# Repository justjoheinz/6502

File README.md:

# 6502 Microcomputer

## Bill of materials

[BOM](6502.csv)

## Schematic

## PCB

### Mainboard

### Prototype Board

### Status

| Version | Status | Comment |
|---------|--------|---------|
| v1.0.0  | unverified | boards send for production |

## Memory maps

| Type | From | To       | Comments |
|------|------|----------|----------|
| RAM  | 0x0000 | 0x3FFF |          |
| VIA  | 0x6000 |        | A14, A15 - Registers via A0 - A3 |
| ROM  | 0x8000 | 0xFFFF | A15 High |

## ROM Source Code

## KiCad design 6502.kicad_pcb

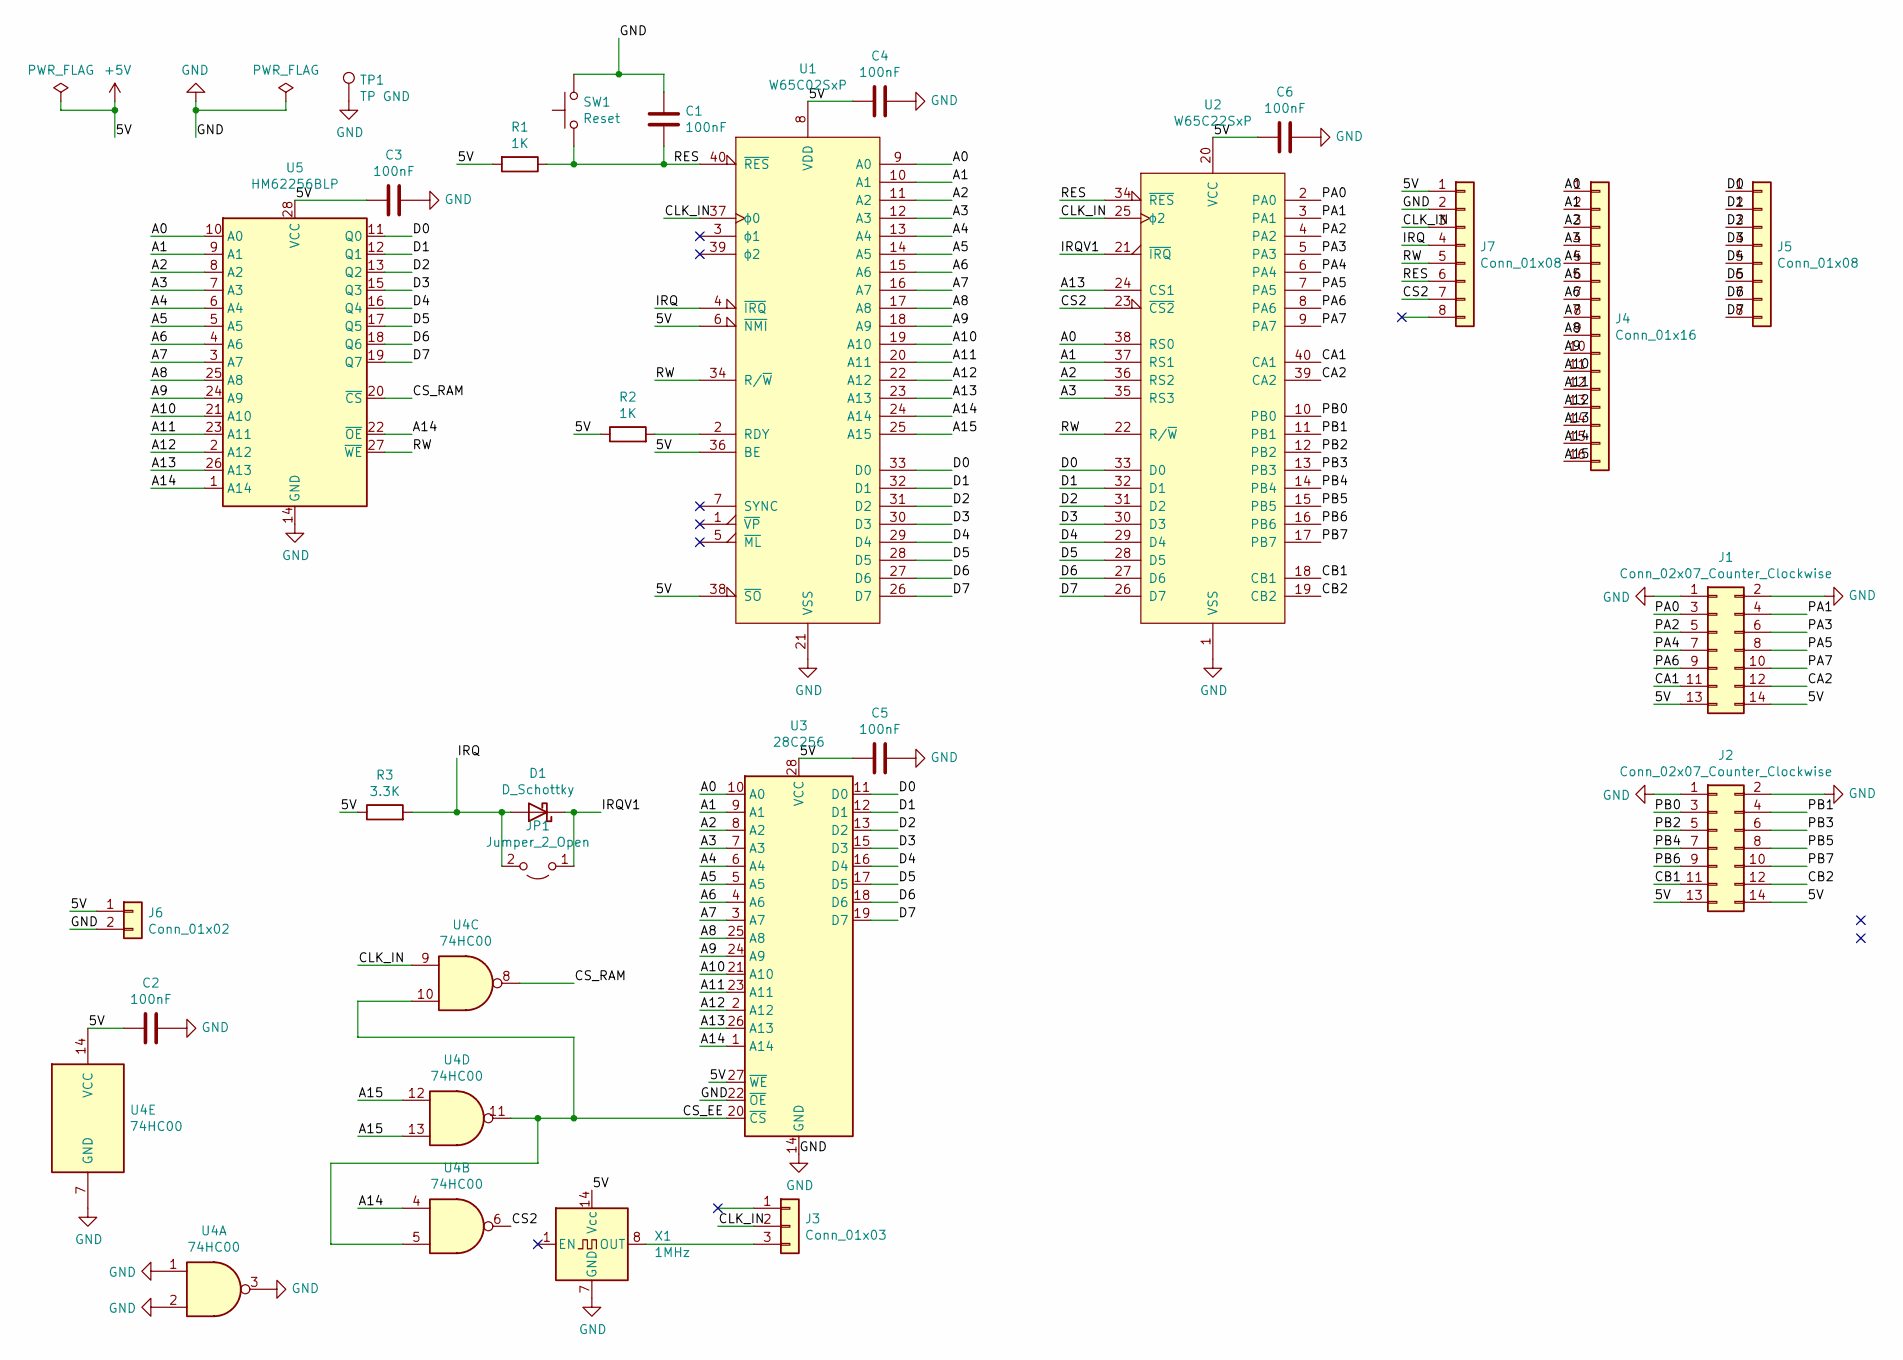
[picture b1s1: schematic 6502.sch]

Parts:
C1, C2, C3, C4, C5, C6: 100nF; C_Disc_D4.3mm_W1.9mm_P5.00mm
D1: D_Schottky; D_DO-35_SOD27_P7.62mm_Horizontal
J1, J2: Conn_02x07_Counter_Clockwise; PinHeader_2x07_P2.54mm_Horizontal
J3: Conn_01x03; PinHeader_1x03_P2.54mm_Vertical
J4: Conn_01x16; PinHeader_1x16_P2.54mm_Vertical
J5, J7: Conn_01x08; PinHeader_1x08_P2.54mm_Vertical
J6: Conn_01x02; PinHeader_1x02_P2.54mm_Vertical
JP1: Jumper_2_Open; TestPoint_2Pads_Pitch2.54mm_Drill0.8mm
R1, R2: 1K; R_Axial_DIN0204_L3.6mm_D1.6mm_P7.62mm_Horizontal
R3: 3.3K; R_Axial_DIN0204_L3.6mm_D1.6mm_P7.62mm_Horizontal
SW1: Reset; SW_PUSH_6mm
TP1: TP GND; TestPoint_Pad_2.0x2.0mm
U1: W65C02SxP; DIP-40_W15.24mm_Socket_LongPads
U2: W65C22SxP; DIP-40_W15.24mm_Socket_LongPads
U3: 28C256; DIP_Socket-28_W11.9_W12.7_W15.24_W17.78_W18.5_3M_228-1277-0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
U4: 74HC00; DIP-14_W7.62mm_Socket_LongPads
U5: HM62256BLP; DIP-28_W15.24mm_Socket_LongPads
X1: 1MHz; Oscillator_DIP-14

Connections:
+5V: C2.2, C3.2, C4.2, C5.1, C6.1, J1.13, J1.14, J2.13, J2.14, J6.1, J7.1, R1.2, R2.1, R3.1, U1.6 (~NMI), U1.8 (VDD), U1.36 (BE), U1.38 (~SO), U2.20 (VCC), U3.27 (~WE), U3.28 (VCC), U4.14 (VCC), U5.28 (VCC), X1.14 (Vcc)
/A0: J4.1, U1.9 (A0), U2.38 (RS0), U3.10 (A0), U5.10 (A0)
/A1: J4.2, U1.10 (A1), U2.37 (RS1), U3.9 (A1), U5.9 (A1)
/A2: J4.3, U1.11 (A2), U2.36 (RS2), U3.8 (A2), U5.8 (A2)
/A3: J4.4, U1.12 (A3), U2.35 (RS3), U3.7 (A3), U5.7 (A3)
/A4: J4.5, U1.13 (A4), U3.6 (A4), U5.6 (A4)
/A5: J4.6, U1.14 (A5), U3.5 (A5), U5.5 (A5)
/A6: J4.7, U1.15 (A6), U3.4 (A6), U5.4 (A6)
/A7: J4.8, U1.16 (A7), U3.3 (A7), U5.3 (A7)
/A8: J4.9, U1.17 (A8), U3.25 (A8), U5.25 (A8)
/A9: J4.10, U1.18 (A9), U3.24 (A9), U5.24 (A9)
/A10: J4.11, U1.19 (A10), U3.21 (A10), U5.21 (A10)
/A11: J4.12, U1.20 (A11), U3.23 (A11), U5.23 (A11)
/A12: J4.13, U1.22 (A12), U3.2 (A12), U5.2 (A12)
/A13: J4.14, U1.23 (A13), U2.24 (CS1), U3.26 (A13), U5.26 (A13)
/A14: J4.15, U1.24 (A14), U3.1 (A14), U4.4, U5.1 (A14), U5.22 (~OE)
/A15: J4.16, U1.25 (A15), U4.12, U4.13
/CA1: J1.11, U2.40 (CA1)
/CA2: J1.12, U2.39 (CA2)
/CB1: J2.11, U2.18 (CB1)
/CB2: J2.12, U2.19 (CB2)
/CLK_IN: J3.2, J7.3, U1.37 (ϕ0), U2.25 (ϕ2), U4.9
/CS2: J7.7, U2.23 (~CS2), U4.6
/CS_EE: U3.20 (~CS), U4.5, U4.10, U4.11
/CS_RAM: U4.8, U5.20 (~CS)
/D0: J5.1, U1.33 (D0), U2.33 (D0), U3.11 (D0), U5.11 (Q0)
/D1: J5.2, U1.32 (D1), U2.32 (D1), U3.12 (D1), U5.12 (Q1)
/D2: J5.3, U1.31 (D2), U2.31 (D2), U3.13 (D2), U5.13 (Q2)
/D3: J5.4, U1.30 (D3), U2.30 (D3), U3.15 (D3), U5.15 (Q3)
/D4: J5.5, U1.29 (D4), U2.29 (D4), U3.16 (D4), U5.16 (Q4)
/D5: J5.6, U1.28 (D5), U2.28 (D5), U3.17 (D5), U5.17 (Q5)
/D6: J5.7, U1.27 (D6), U2.27 (D6), U3.18 (D6), U5.18 (Q6)
/D7: J5.8, U1.26 (D7), U2.26 (D7), U3.19 (D7), U5.19 (Q7)
/IRQ: D1.2 (A), J7.4, JP1.2 (B), R3.2, U1.4 (~IRQ)
/IRQV1: D1.1 (K), JP1.1 (A), U2.21 (~IRQ)
/PA0: J1.3, U2.2 (PA0)
/PA1: J1.4, U2.3 (PA1)
/PA2: J1.5, U2.4 (PA2)
/PA3: J1.6, U2.5 (PA3)
/PA4: J1.7, U2.6 (PA4)
/PA5: J1.8, U2.7 (PA5)
/PA6: J1.9, U2.8 (PA6)
/PA7: J1.10, U2.9 (PA7)
/PB0: J2.3, U2.10 (PB0)
/PB1: J2.4, U2.11 (PB1)
/PB2: J2.5, U2.12 (PB2)
/PB3: J2.6, U2.13 (PB3)
/PB4: J2.7, U2.14 (PB4)
/PB5: J2.8, U2.15 (PB5)
/PB6: J2.9, U2.16 (PB6)
/PB7: J2.10, U2.17 (PB7)
/RES: C1.2, J7.6, R1.1, SW1.1, U1.40 (~RES), U2.34 (~RES)
/RW: J7.5, U1.34 (R/~W), U2.22 (R/~W), U5.27 (~WE)
GND: C1.1, C2.1, C3.1, C4.1, C5.2, C6.2, J1.1, J1.2, J2.1, J2.2, J6.2, J7.2, SW1.2, TP1.1, U1.21 (VSS), U2.1 (VSS), U3.14 (GND), U3.22 (~OE), U4.1, U4.2, U4.3, U4.7 (GND), U5.14 (GND), X1.7 (GND)
unnamed: J3.3, X1.8 (OUT)
unnamed: R2.2, U1.2 (RDY)

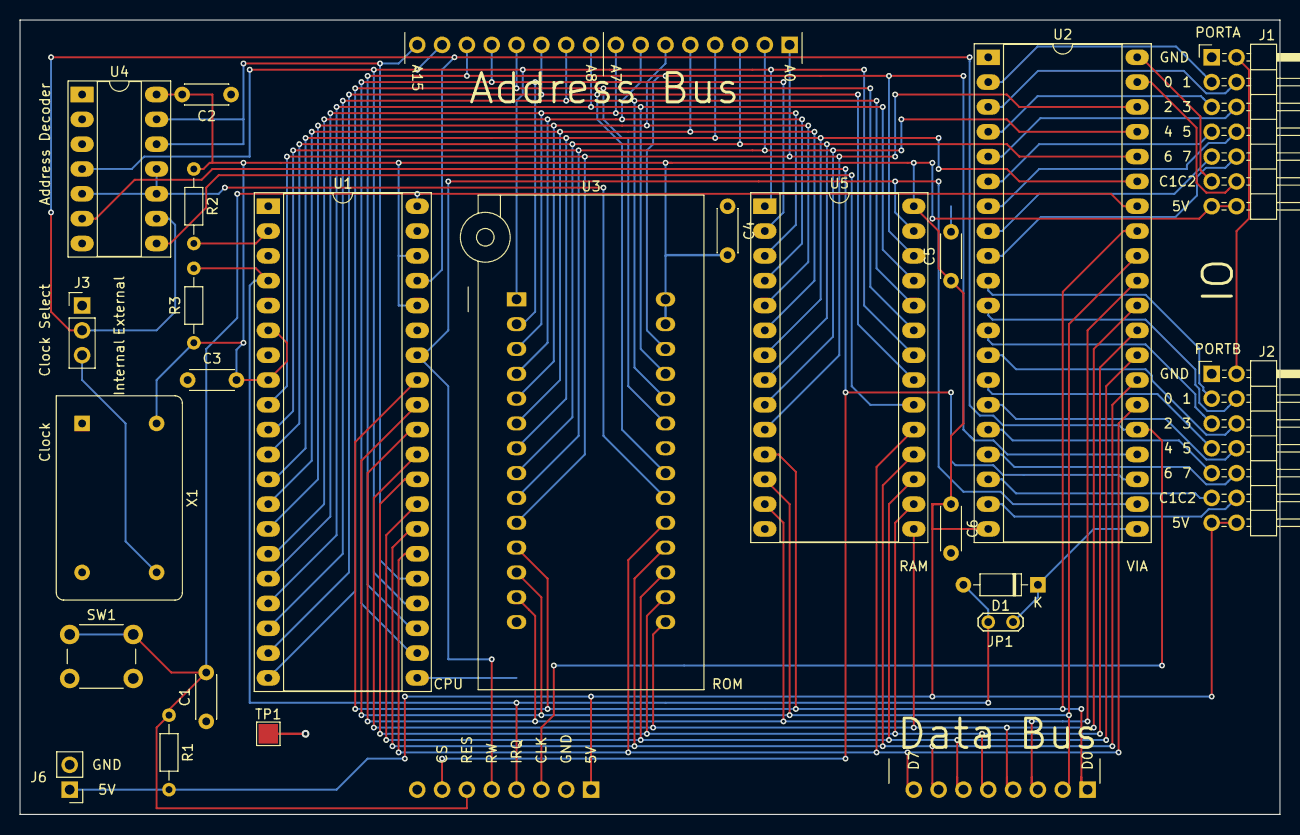
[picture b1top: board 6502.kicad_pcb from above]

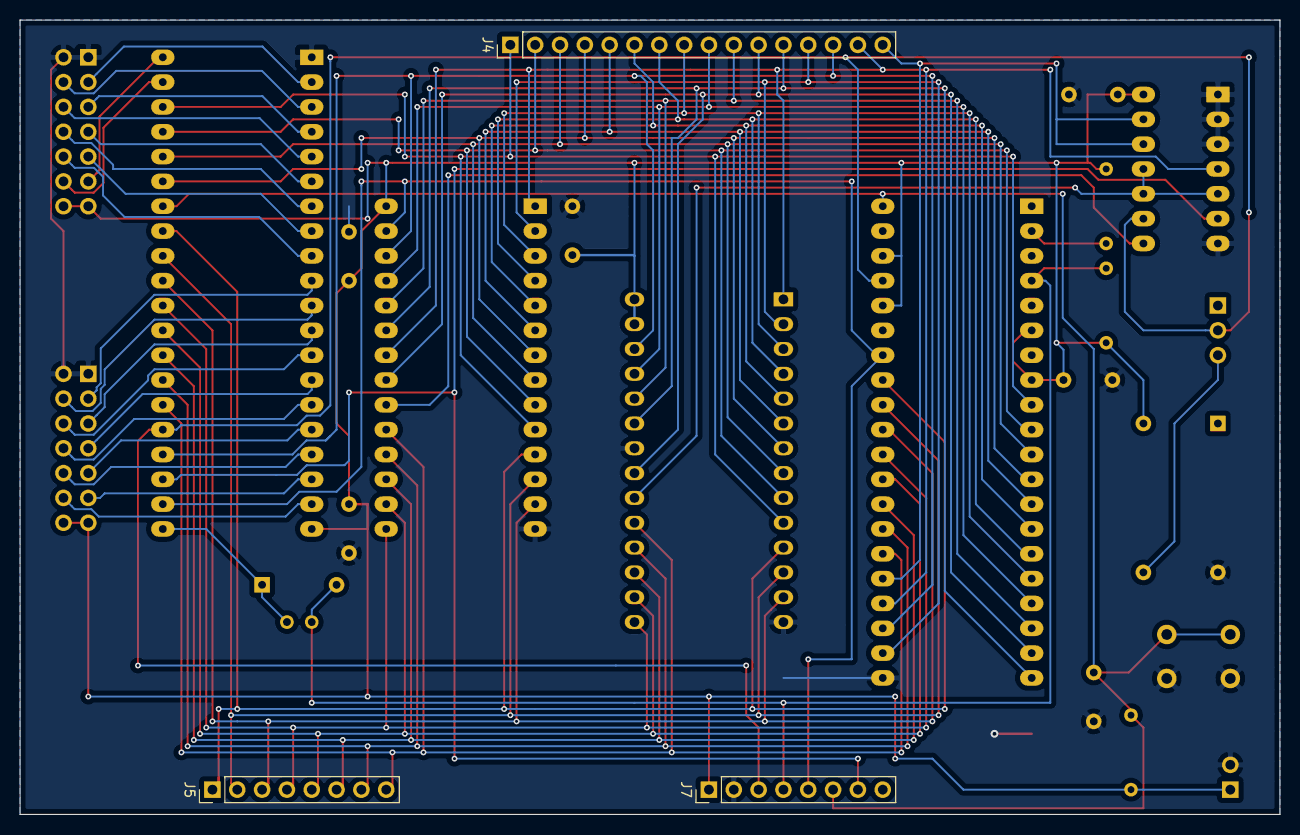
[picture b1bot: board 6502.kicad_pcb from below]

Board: 2 copper layers, 128.9 x 81.3 mm, 26 parts (3 on the bottom side), 56 nets.

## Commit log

2020-11-22 Initial version
2020-11-22 Better .gitignore file
2020-11-22 Add README.md
2020-11-22 Remove fp-info-cache from repo
2020-11-22 Add BOM
2020-11-22 Add memory map
2020-11-24 Removed pinheaders from 3D view
2020-11-26 Add power supply text to silkscreen
